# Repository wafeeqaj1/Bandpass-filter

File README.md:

# Bandpass-filter
Authors: Wafeeq Jaleel, Tianxiang He

## Description
This was a project done for ECE 3090:Technical writing and presentation at the Ohio state university. Simulated passive elements in a band pass filter using TopSpice to obtain element values for 200kHz center frequency and 50kHz bandwidth then designed the PCB in KiCad based on the values. 

### Dependencies
* TopSpice (latest version)
* KiCad

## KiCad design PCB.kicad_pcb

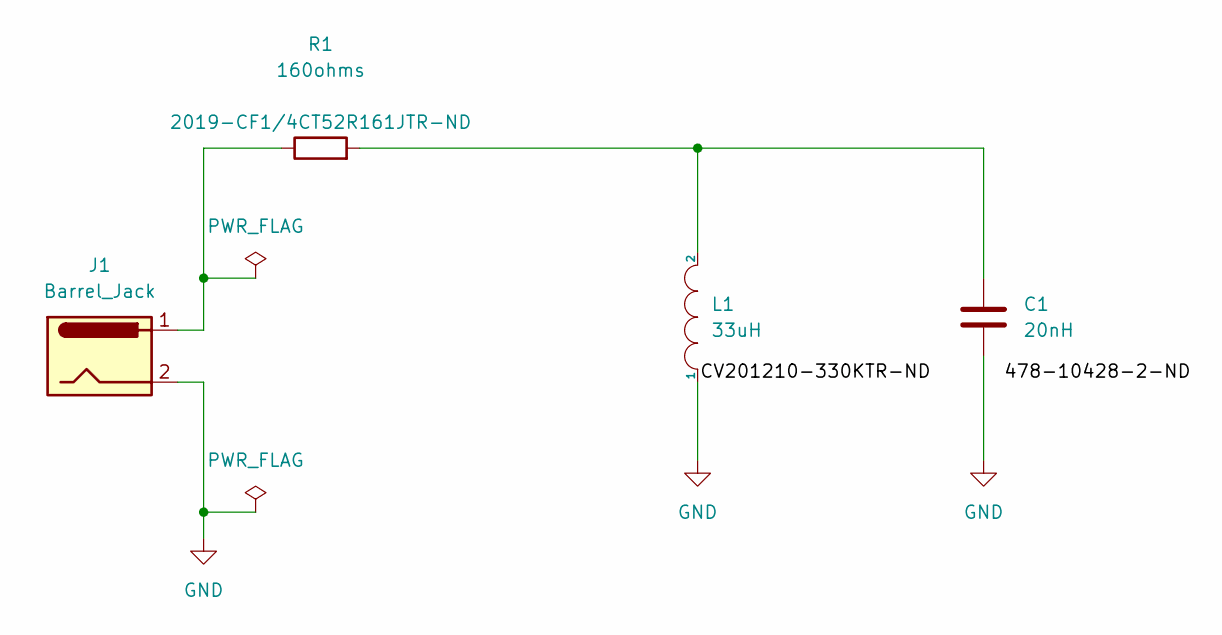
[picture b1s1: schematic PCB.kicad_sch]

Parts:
C1: 20nH; C_0805_2012Metric
J1: Barrel_Jack; BarrelJack_CUI_PJ-102AH_Horizontal
L1: 33uH; L_0805_2012Metric
R1: 160ohms; R_Axial_DIN0207_L6.3mm_D2.5mm_P7.62mm_Horizontal; Digikey # 2019-CF1/4CT52R161JTR-ND

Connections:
GND: C1.2, J1.2, L1.1
unnamed: C1.1, L1.2, R1.2
unnamed: J1.1, R1.1

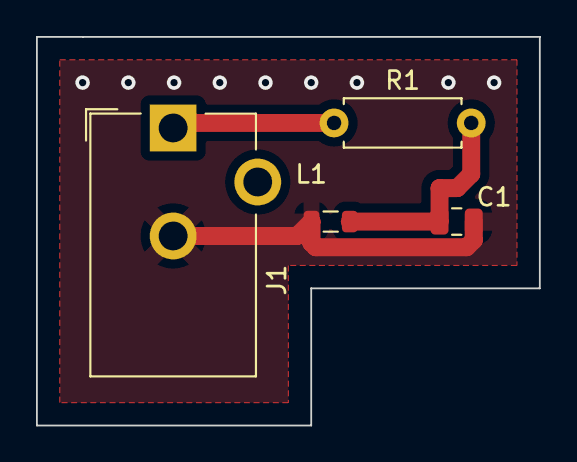
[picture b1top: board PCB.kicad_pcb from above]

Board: 2 copper layers, 27.9 x 21.6 mm, 4 parts (0 on the bottom side), 3 nets.

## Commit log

2023-01-15 Reports
2023-01-15 Design files
2023-01-15 PCB design
